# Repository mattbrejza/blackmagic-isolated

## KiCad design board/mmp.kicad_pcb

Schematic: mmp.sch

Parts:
C1, C4: C_Small; C_0603
C2, C3, C5, C6, C10, C12, C18, C19: 100n; C_0603
C7, C9, C11, C13, C14: 4.7u; C_0603
C8: 1u; C_0603
C15, C17: 10u; C_0805
C16: 470p 4kV
D1, D2, D3, D4, D5, D6: LED; LED-0603
IC1: STM32F103C; LQFP-48_7x7mm_Pitch0.5mm
IC2, IC3: SI8662; SO-16-N
IC4, IC5: MCP1700-33; SOT-23; Farnell 2363085/1296592
IC6: TXS0108; TSSOP-20_4.4x6.5mm_Pitch0.65mm
IC7: 1117-SOT223; SOT-223
J1: SWD; Pin_Header_Straight_2x05_Pitch1.27mm
L1: 4.7u; Neosid_Inductor_SM-NE30_SMD1210; Farnell 2451985/2292513
P1: USB_B; USB_Mini-B
P2: CONN_01X04; Connector_Molex_PicoBlade_53261-0471
P3: TC2030-CTX; TC2030-NL_SMALL
Q1: 2n2007; SOT-23; Farnell 1510761
Q2: NTR4101; SOT-23; Farnell 1431303
R1, R6, R15, R19: 10k; C0603-N
R2: 1.5k; C0603-N
R3, R4: 22; C0603-N
R5, R12, R13, R14, R16, R17, R18, R21, R22: 4.7k; C0603-N
R7, R8, R9, R10, R11, R20: 330; C0603-N
SW1, SW3: SW_PUSH; SW_SPST_EVQPE1
SW2: SP3T; AYZ0103AGRLC; Farnell 2319972
U2: ROE-0505S; ROE-DCDC
Y1: Crystal_Small; ABM7

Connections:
+3.3VP: C12.1, C13.1, C19.1, IC2.16 (VDD2), IC3.16 (VDD2), IC5.2, IC6.19, IC6.20
+3V3: C2.1, C3.1, C5.1, C6.1, C8.1, C9.1, C10.1, C18.1, D4.2 (A), IC1.1 (VBAT), IC1.9 (VDDA), IC1.24 (VDD), IC1.36 (VDD), IC1.40 (PB4), IC1.41 (PB5), IC1.48 (VDD), IC2.1 (VDD1), IC3.1 (VDD1), IC4.2, P3.1, R1.2, SW3.1
+5VP: C11.1, C14.1, C16.1, IC5.3, IC7.3, U2.4 (Vout+)
/H_RST: IC1.7 (NRST), P3.3
/H_SWCLK: IC1.30 (PA9), IC1.37 (PA14), IC2.3 (A2), P3.4
/H_SWDIO: IC1.31 (PA10), IC1.34 (PA13), IC2.5 (A4), P3.2, R21.1
/LED0: D1.2 (A), IC1.20 (PB2)
/LED1: D2.2 (A), IC1.21 (PB10)
/LED2: D3.2 (A), IC1.22 (PB11)
/PWR_BR: IC1.19 (PB1), IC2.4 (A3)
/PWR_BR_IS: D6.2 (A), IC2.13 (B3), Q1.1 (G)
/REGOUT: C17.1, IC7.2, IC7.4, Q2.3 (S), R14.1, R16.1, R18.1, R19.1
/RST: IC1.12 (PA2), IC3.3 (A2)
/Rx: IC6.4, P2.2
/SWCLK: IC1.15 (PA5), IC3.2 (A1)
/SWDIO: IC1.14 (PA4), IC3.5 (A4), R12.1
/SWO: IC1.16 (PA6), IC3.7 (A6)
/TDI: IC1.13 (PA3), IC3.4 (A3)
/TPWR: D5.2 (A), IC6.2, IC6.10, J1.1, P2.4, Q2.1 (D)
/Tx: IC6.3, P2.3
/Vbus: C7.1, C15.1, IC4.3, L1.1, P1.1 (VCC), R5.1
GNDREF: C11.2, C12.2, C13.2, C14.2, C17.2, C19.2, IC2.9 (GND2), IC2.11 (B5), IC3.9 (GND2), IC5.1, IC6.11, J1.3, J1.5, J1.9, P2.1, Q1.2 (S), R7.2, R17.2, R20.2, U2.3 (Vout-)
unnamed: C1.1, IC1.5 (PD0), Y1.1
unnamed: C4.1, IC1.6 (PD1), Y1.2
unnamed: C16.2, L1.2, U2.2 (Vin+)
unnamed: D1.1 (K), R8.1
unnamed: D2.1 (K), R9.1
unnamed: D3.1 (K), R10.1
unnamed: D4.1 (K), R11.1
unnamed: D5.1 (K), R7.1
unnamed: D6.1 (K), R20.1
unnamed: IC1.25 (PB12), R1.1, SW1.1
unnamed: IC1.26 (PB13), R5.2, R6.1
unnamed: IC1.29 (PA8), R2.1
unnamed: IC1.32 (PA11), R3.1
unnamed: IC1.33 (PA12), R4.2
unnamed: IC1.44 (BOOT0), R15.2, SW3.2
unnamed: IC2.7 (A6), R21.2
unnamed: IC2.10 (B6), IC6.17, R22.2
unnamed: IC2.12 (B4), R22.1
unnamed: IC2.14 (B2), IC6.18
unnamed: IC3.6 (A5), R12.2
unnamed: IC3.10 (B6), IC6.16
unnamed: IC3.11 (B5), IC6.15, R13.2
unnamed: IC3.12 (B4), R13.1
unnamed: IC3.13 (B3), IC6.14
unnamed: IC3.14 (B2), IC6.13
unnamed: IC3.15 (B1), IC6.12
unnamed: IC6.5, J1.6
unnamed: IC6.6, J1.2
unnamed: IC6.7, J1.8
unnamed: IC6.8, J1.10
unnamed: IC6.9, J1.4
unnamed: IC7.1, R14.2, R17.1, SW2.3
unnamed: P1.2 (D-), R3.2
unnamed: P1.3 (D+), R2.2, R4.1
unnamed: Q1.3 (D), Q2.2 (G), R19.2
unnamed: R16.2, SW2.2
unnamed: R18.2, SW2.4

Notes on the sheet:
check these!
correct fp?

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
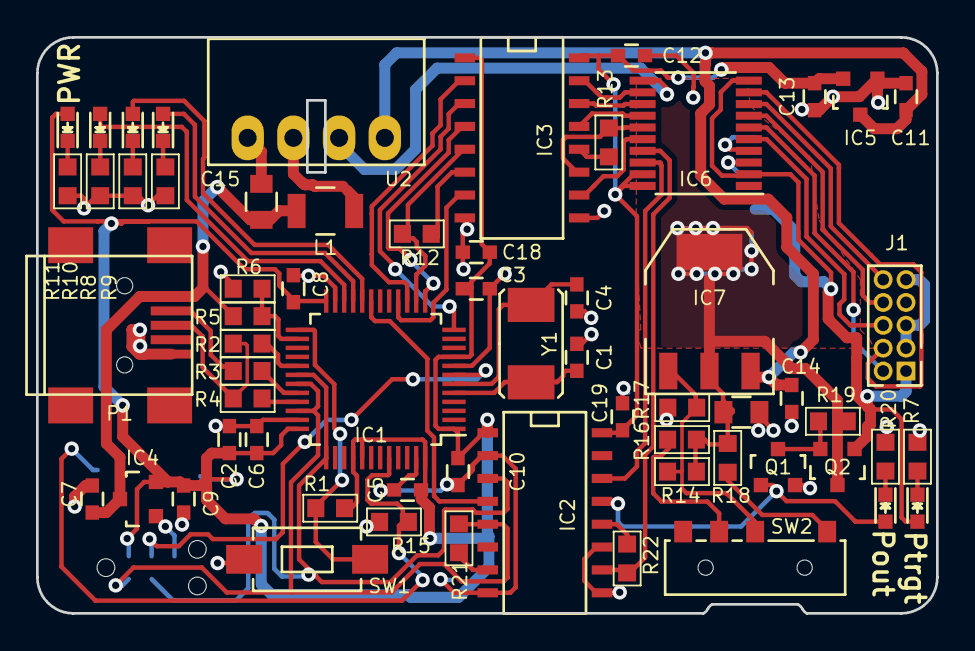
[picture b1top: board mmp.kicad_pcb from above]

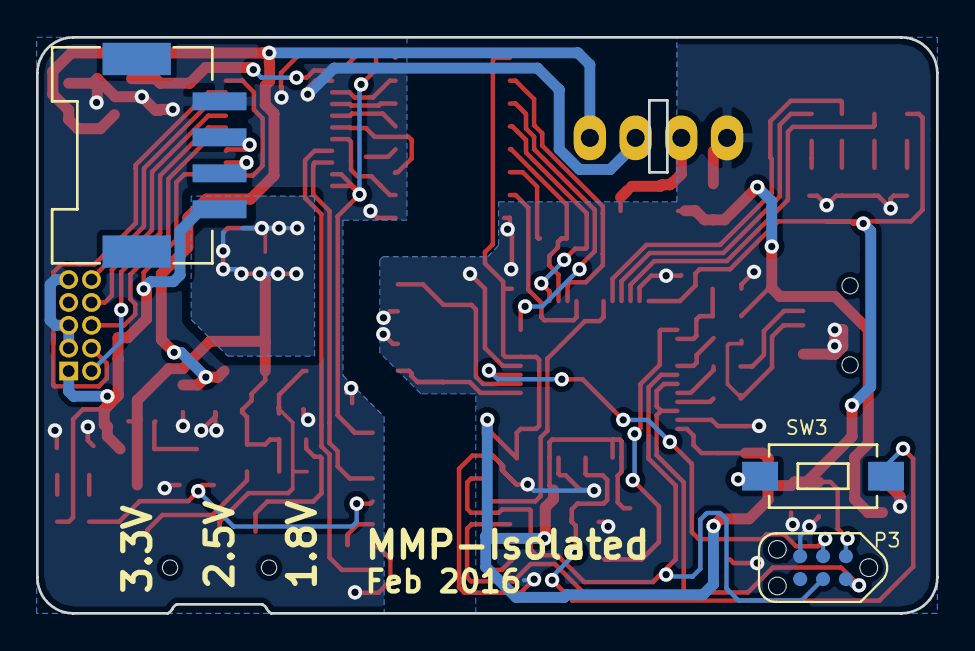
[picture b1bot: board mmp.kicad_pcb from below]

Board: 2 copper layers, 50.0 x 32.0 mm, 65 parts (3 on the bottom side), 60 nets.

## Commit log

2015-11-09 mostly done
2015-11-15 finishing off
2016-02-17 done
2016-02-17 adding gerbers
